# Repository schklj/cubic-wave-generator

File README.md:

# cubic-wave-generator
usb very low frequency square wave generator with low output impedance, fixed at 50% duty cycle

soldering pads are enlarged to make it more optimized for a more *banausic* pcb fabrication techniques can size 55*44

# ideas for improvement 
* adding n-fet to the output amplification circuit
* feeding the the output amplification from the bjt totem pole instead of timer output
* intoducing h-brige to remove the dc offset in the output signal
* making it based on AD9833 with digital control

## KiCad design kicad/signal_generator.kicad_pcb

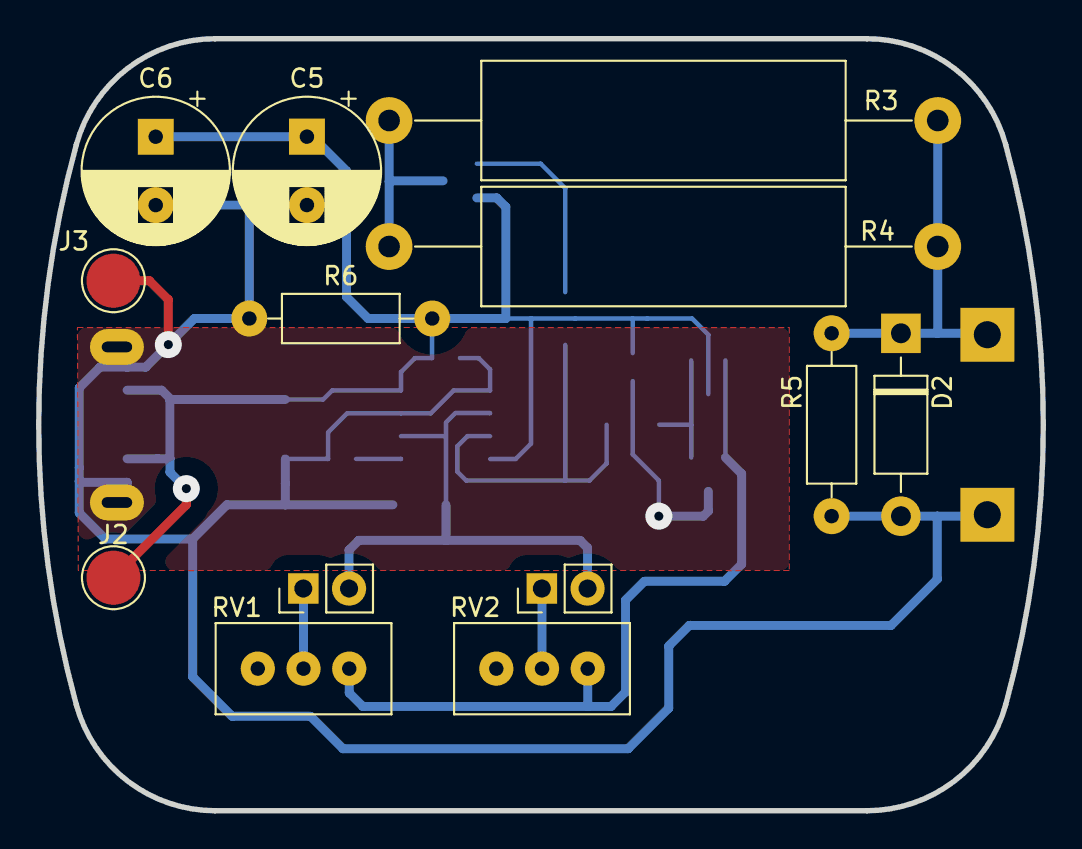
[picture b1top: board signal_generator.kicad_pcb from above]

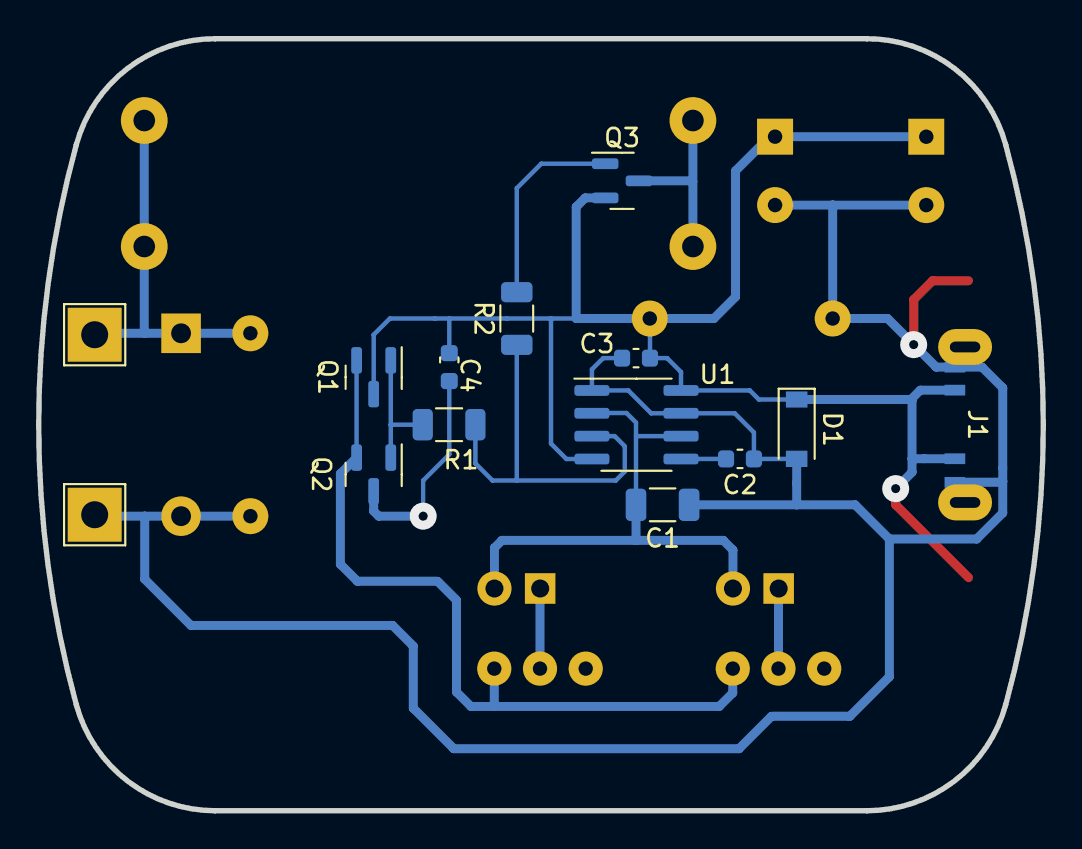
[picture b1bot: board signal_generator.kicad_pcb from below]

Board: 2 copper layers, 55.8 x 42.9 mm, 27 parts (14 on the bottom side), 12 nets.

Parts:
C1: 68n; C_1206_3216Metric
C2: 0.01u; C_0603_1608Metric
C3, C4: 0.1u; C_0603_1608Metric
C5, C6: 220u; CP_Radial_D8.0mm_P3.80mm
D1: 5.1; D_SOD-123
D2: IN4007; D_DO-41_SOD81_P10.16mm_Horizontal
J1: USB_C_Receptacle_USB2.0; USB_C_Receptacle_XKB_U262-16XN-4BVC11
J2: VCC; TestPoint_Pad_D3.0mm
J3: GND; TestPoint_Pad_D3.0mm
J4: SIGNAL; TestPoint_THTPad_3.0x3.0mm_Drill1.5mm
J5: GND; TestPoint_THTPad_3.0x3.0mm_Drill1.5mm
J6: 2M_tp; PinHeader_1x02_P2.54mm_Vertical
J7: 50k_tp; PinHeader_1x02_P2.54mm_Vertical
Q1: S8050; SOT-23
Q2: S8550; SOT-23
Q3: AO3401A; SOT-23
R1: 80; R_1206_3216Metric
R2: 50; R_1206_3216Metric
R3, R4: 5.1Ohm; 3W; R_Axial_Power_L20.0mm_W6.4mm_P30.48mm
R5, R6: 5k; R_Axial_DIN0207_L6.3mm_D2.5mm_P10.16mm_Horizontal
RV1: 2M; Potentiometer_Bourns_3296W_Vertical
RV2: 50k; Potentiometer_Bourns_3296W_Vertical
U1: LMC555; SOIC-8_3.9x4.9mm_P1.27mm

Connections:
+5V: C3.2, C4.2, C5.1, C6.1, D1.1 (K), J1.A4 (VBUS), J2.1, Q1.3 (C), Q3.2 (S), R6.2, U1.4 (R), U1.8 (VCC)
GND: C1.1, C2.1, C3.1, C4.1, C5.2, C6.2, D1.2 (A), D2.2 (A), J1.A1 (GND), J1.S1 (SHIELD), J3.1, J5.1, Q2.3 (C), R5.1, R6.1, U1.1 (GND), U1.7 (DIS)
unnamed: C1.2, J6.2, J7.2, U1.2 (TR), U1.6 (THR)
unnamed: C2.2, U1.5 (CV)
unnamed: D2.1 (K), J4.1, R3.1, R4.1, R5.2
unnamed: J6.1, RV1.2
unnamed: J7.1, RV2.2
unnamed: Q1.1 (B), Q2.1 (B), R1.2
unnamed: Q1.2 (E), Q2.2 (E), RV1.1, RV2.1
unnamed: Q3.1 (G), R2.2
unnamed: Q3.3 (D), R3.2, R4.2
unnamed: R1.1, R2.1, U1.3 (Q)

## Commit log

2023-06-13 Initial commit
    cubic signal generator design
2023-06-15 extended description
